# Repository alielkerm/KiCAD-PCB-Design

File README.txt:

# Project Name

KiCAD PCB Designs

## Overview
This directory shows some personal as well as professional projects in PCB design using KiCAD open source tool.

## Context
Academic / personal project related to space electronics, payload design, amateur boards for learning and teaching to bachelor and master students.

## Technologies
- KiCAD

## Results
Boards are ready to be sent to the manufacturing house, once the PCB boards are fabricated, I will share the physical boards, the tests and the results of the tests.

## Author
Ali Elkerm

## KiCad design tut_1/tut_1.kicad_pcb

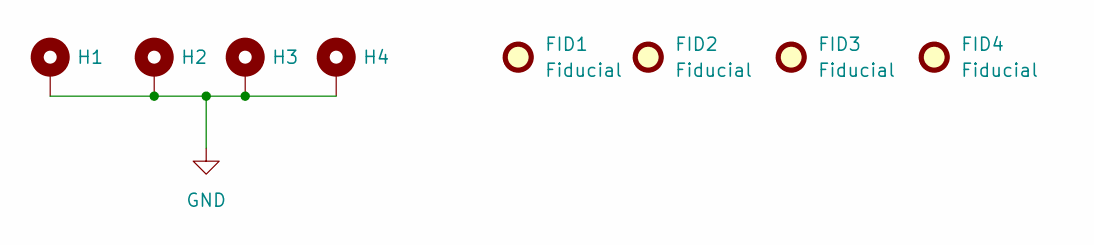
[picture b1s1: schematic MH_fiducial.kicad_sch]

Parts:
FID1, FID2, FID3, FID4: Fiducial; Fiducial_1.5mm_Mask3mm
H1, H2, H3, H4: MountingHole_Pad; MountingHole_2.5mm_Pad

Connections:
GND: H1.1, H2.1, H3.1, H4.1; also elsewhere on the board

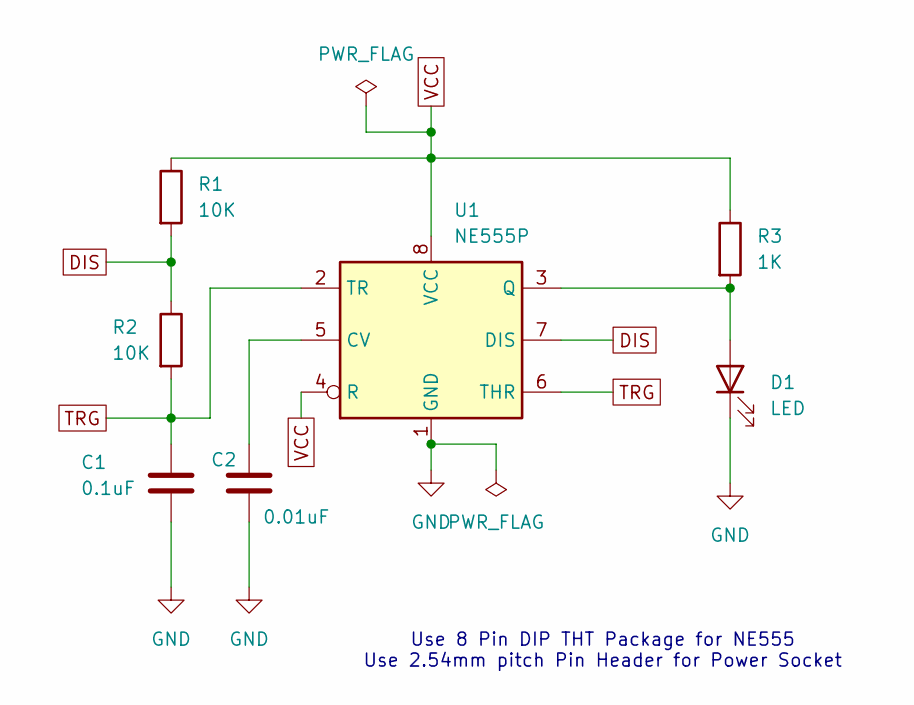
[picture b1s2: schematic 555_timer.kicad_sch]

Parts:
C1: 0.1uF; C_0603_1608Metric
C2: 0.01uF; C_0603_1608Metric
D1: LED; LED_0603_1608Metric
R1, R2: 10K; R_0603_1608Metric
R3: 1K; R_0603_1608Metric
U1: NE555P; SOP-8_3.76x4.96mm_P1.27mm

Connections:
DIS: R1.2, R2.1, U1.7 (DIS)
GND: C1.2, C2.2, D1.1 (K), U1.1 (GND); also elsewhere on the board
unnamed: D1.2 (A), R3.2, U1.3 (Q)
unnamed: C2.1, U1.5 (CV)
TRG: C1.1, R2.2, U1.2 (TR), U1.6 (THR)
VCC: R1.1, R3.1, U1.4 (R), U1.8 (VCC); also elsewhere on the board

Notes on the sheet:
Use 8 Pin DIP THT Package for NE555 Use 2.54mm pitch Pin Header for Power Socket

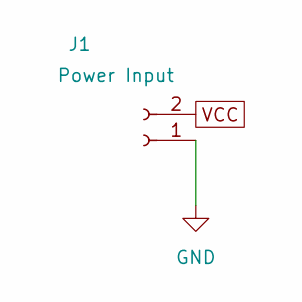
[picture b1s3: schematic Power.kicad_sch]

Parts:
J1: Power Input; PinHeader_1x02_P2.54mm_Vertical

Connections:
GND: J1.1; also elsewhere on the board
VCC: J1.2; also elsewhere on the board

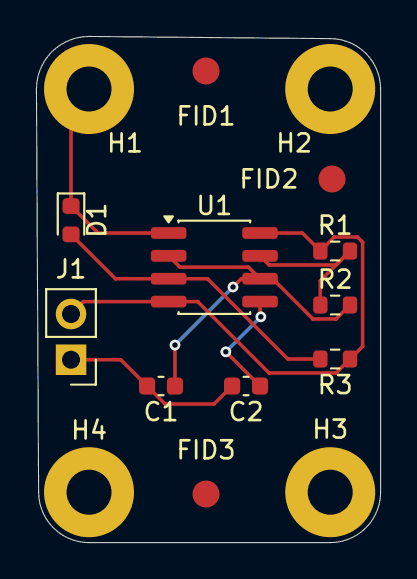
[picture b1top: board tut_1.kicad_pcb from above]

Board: 2 copper layers, 19.1 x 28.1 mm, 15 parts (0 on the bottom side), 6 nets.

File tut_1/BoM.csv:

"Reference","Qty","Value","DNP","Exclude from BOM","Exclude from Board","Footprint","Datasheet"
"C1","1","0.1uF","","","","Capacitor_SMD:C_0603_1608Metric","~"
"C2","1","0.01uF","","","","Capacitor_SMD:C_0603_1608Metric","~"
"D1","1","LED","","","","LED_SMD:LED_0603_1608Metric","~"
"FID1,FID2,FID3,FID4","4","Fiducial","","Excluded from BOM","","Fiducial:Fiducial_1.5mm_Mask3mm","~"
"H1,H2,H3,H4","4","MountingHole_Pad","","Excluded from BOM","","MountingHole:MountingHole_2.5mm_Pad","~"
"J1","1","Power Input","","","","Connector_PinHeader_2.54mm:PinHeader_1x02_P2.54mm_Vertical","~"
"R1,R2","2","10K","","","","Resistor_SMD:R_0603_1608Metric","~"
"R3","1","1K","","","","Resistor_SMD:R_0603_1608Metric","~"
"U1","1","NE555P","","","","Package_SO:SOP-8_3.76x4.96mm_P1.27mm","http://www.ti.com/lit/ds/symlink/ne555.pdf"

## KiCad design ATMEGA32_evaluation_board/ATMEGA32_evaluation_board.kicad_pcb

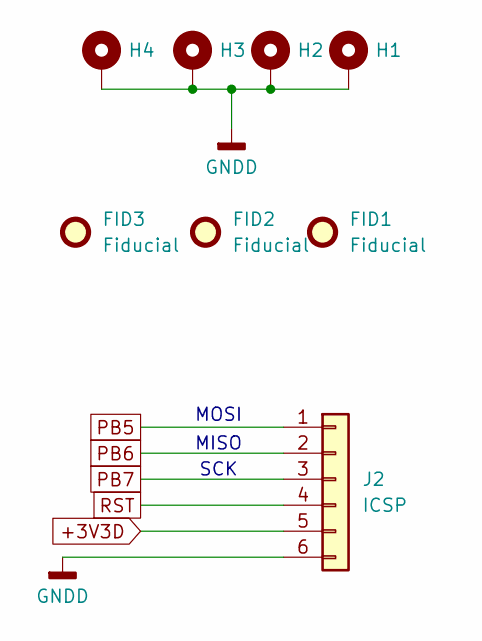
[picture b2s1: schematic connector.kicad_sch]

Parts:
FID1, FID2, FID3: Fiducial; Fiducial_1.5mm_Mask3mm
H1, H2, H3, H4: MountingHole_Pad; MountingHole_2.5mm_Pad
J2: ICSP; PinHeader_1x06_P2.54mm_Vertical

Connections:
+3V3D: J2.5; also elsewhere on the board
GNDD: H1.1, H2.1, H3.1, H4.1, J2.6; also elsewhere on the board
PB5: J2.1; also elsewhere on the board
PB6: J2.2; also elsewhere on the board
PB7: J2.3; also elsewhere on the board
RST: J2.4; also elsewhere on the board

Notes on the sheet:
MISO
MOSI
SCK

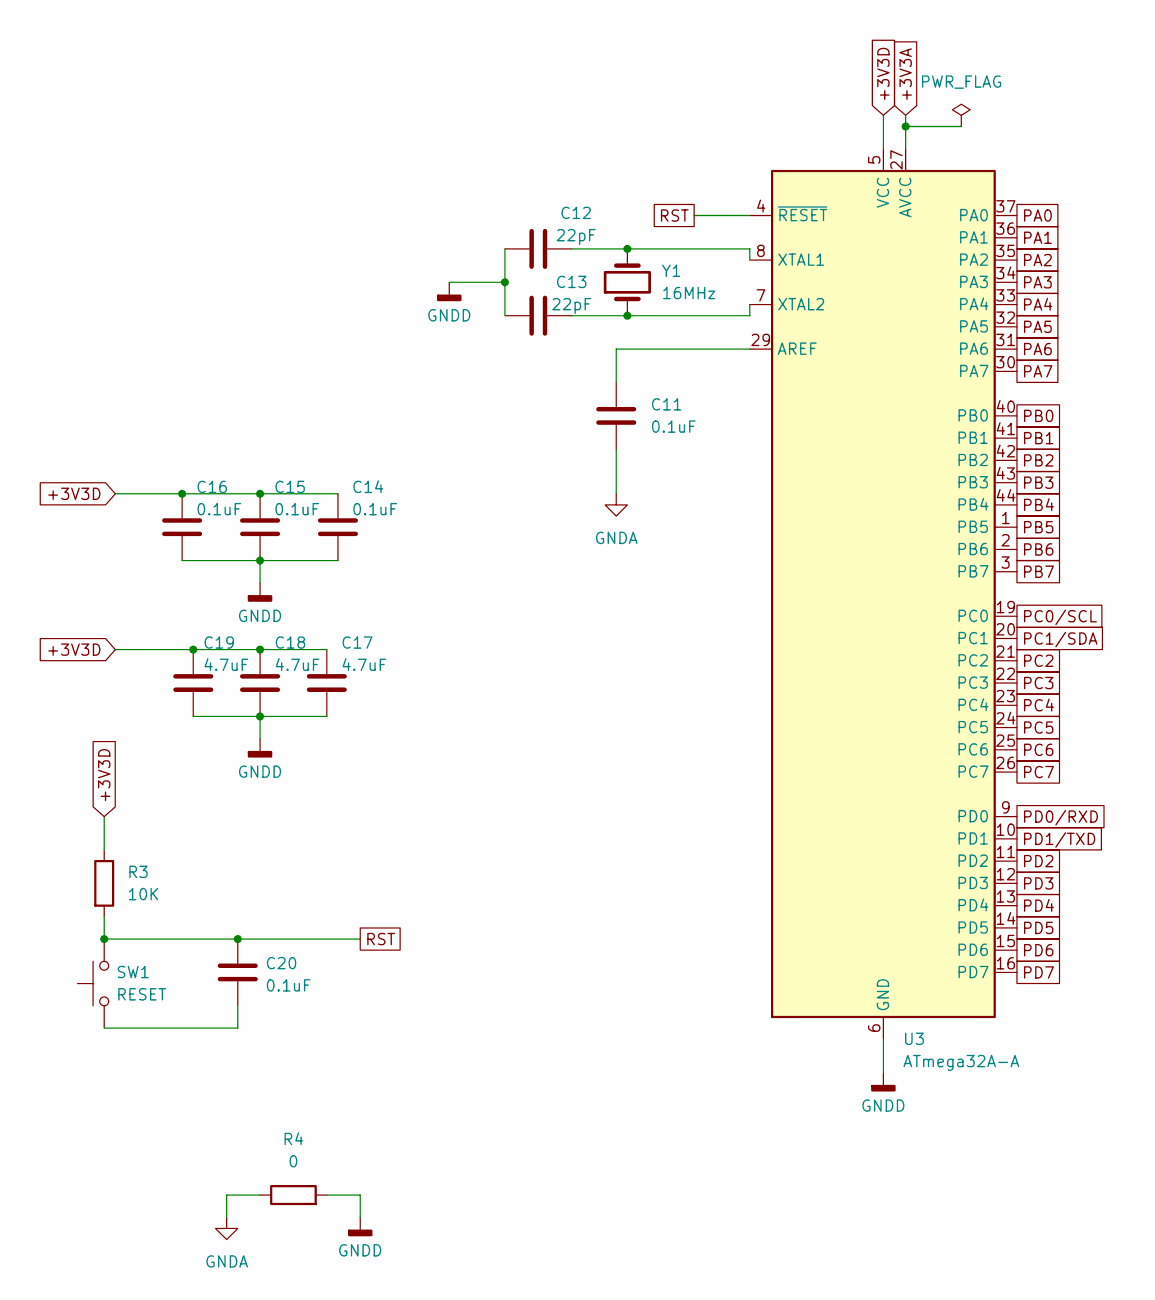
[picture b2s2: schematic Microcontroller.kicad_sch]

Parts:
C11, C14, C15, C16, C20: 0.1uF; C_0603_1608Metric
C12, C13: 22pF; C_0603_1608Metric
C17, C18, C19: 4.7uF; C_0603_1608Metric
R3: 10K; R_0603_1608Metric
R4: 0; R_0603_1608Metric
SW1: RESET; SW_PUSH_6mm
U3: ATmega32A-A; TQFP-44_10x10mm_P0.8mm
Y1: 16MHz; Crystal_SMD_0603-2Pin_6.0x3.5mm

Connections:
+3V3A: U3.27 (AVCC); also elsewhere on the board
+3V3D: C14.1, C15.1, C16.1, C17.1, C18.1, C19.1, R3.1, U3.5 (VCC), U3.17 (VCC), U3.38 (VCC); also elsewhere on the board
GNDA: C11.2, R4.1; also elsewhere on the board
GNDD: C12.1, C13.2, C14.2, C15.2, C16.2, C17.2, C18.2, C19.2, R4.2, U3.6 (GND), U3.18 (GND), U3.28 (GND), U3.39 (GND); also elsewhere on the board
unnamed: C20.2, SW1.1
unnamed: C11.1, U3.29 (AREF)
unnamed: C12.2, U3.8 (XTAL1), Y1.2
unnamed: C13.1, U3.7 (XTAL2), Y1.1
PA0: U3.37 (PA0)
PA1: U3.36 (PA1)
PA2: U3.35 (PA2)
PA3: U3.34 (PA3)
PA4: U3.33 (PA4)
PA5: U3.32 (PA5)
PA6: U3.31 (PA6)
PA7: U3.30 (PA7)
PB0: U3.40 (PB0)
PB1: U3.41 (PB1)
PB2: U3.42 (PB2)
PB3: U3.43 (PB3)
PB4: U3.44 (PB4)
PB5: U3.1 (PB5); also elsewhere on the board
PB6: U3.2 (PB6); also elsewhere on the board
PB7: U3.3 (PB7); also elsewhere on the board
PC0/SCL: U3.19 (PC0)
PC1/SDA: U3.20 (PC1)
PC2: U3.21 (PC2)
PC3: U3.22 (PC3)
PC4: U3.23 (PC4)
PC5: U3.24 (PC5)
PC6: U3.25 (PC6)
PC7: U3.26 (PC7)
PD0/RXD: U3.9 (PD0)
PD1/TXD: U3.10 (PD1)
PD2: U3.11 (PD2)
PD3: U3.12 (PD3)
PD4: U3.13 (PD4)
PD5: U3.14 (PD5)
PD6: U3.15 (PD6)
PD7: U3.16 (PD7)
RST: C20.1, R3.2, SW1.2, U3.4 (~RESET); also elsewhere on the board

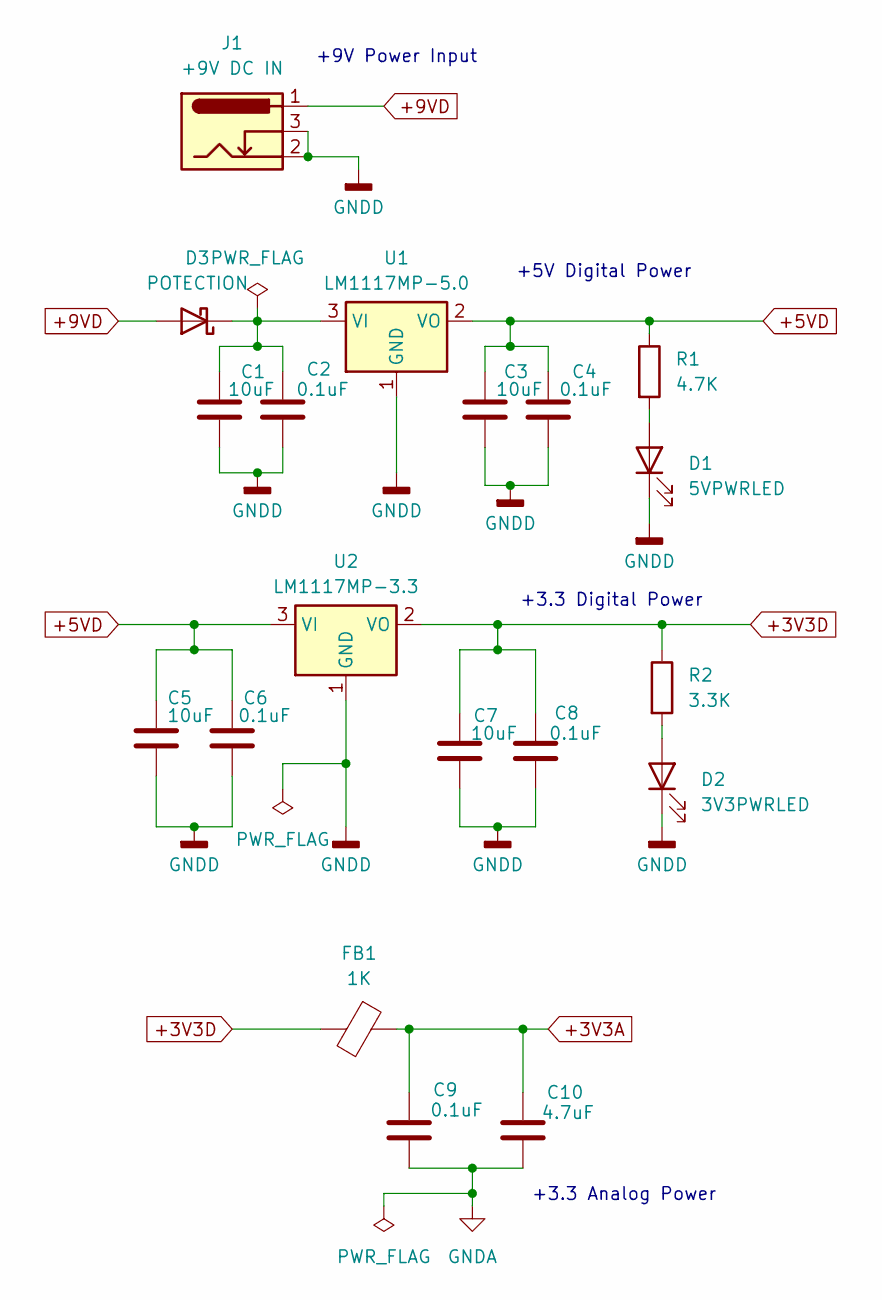
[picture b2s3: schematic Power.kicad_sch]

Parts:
C1, C3, C5, C7: 10uF; C_0603_1608Metric
C2, C4, C6, C8, C9: 0.1uF; C_0603_1608Metric
C10: 4.7uF; C_0603_1608Metric
D1: 5VPWRLED; LED_0603_1608Metric
D2: 3V3PWRLED; LED_0603_1608Metric
D3: POTECTION; D_SMA
FB1: 1K; L_0603_1608Metric
J1: +9V DC IN; PinHeader_1x03_P2.54mm_Vertical
R1: 4.7K; R_0603_1608Metric
R2: 3.3K; R_0603_1608Metric
U1: LM1117MP-5.0; SOT-223-3_TabPin2
U2: LM1117MP-3.3; SOT-223-3_TabPin2

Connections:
+3V3A: C9.1, C10.1, FB1.1; also elsewhere on the board
+3V3D: C7.1, C8.1, FB1.2, R2.1, U2.2 (VO); also elsewhere on the board
+5VD: C3.1, C4.1, C5.1, C6.1, R1.1, U1.2 (VO), U2.3 (VI)
+9VD: D3.2 (A), J1.1
GNDA: C9.2, C10.2; also elsewhere on the board
GNDD: C1.2, C2.2, C3.2, C4.2, C5.2, C6.2, C7.2, C8.2, D1.1 (K), D2.1 (K), J1.2, J1.3, U1.1 (GND), U2.1 (GND); also elsewhere on the board
unnamed: D1.2 (A), R1.2
unnamed: D2.2 (A), R2.2
unnamed: C1.1, C2.1, D3.1 (K), U1.3 (VI)

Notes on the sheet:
+9V Power Input
+5V Digital Power
+3.3 Analog Power
+3.3 Digital Power

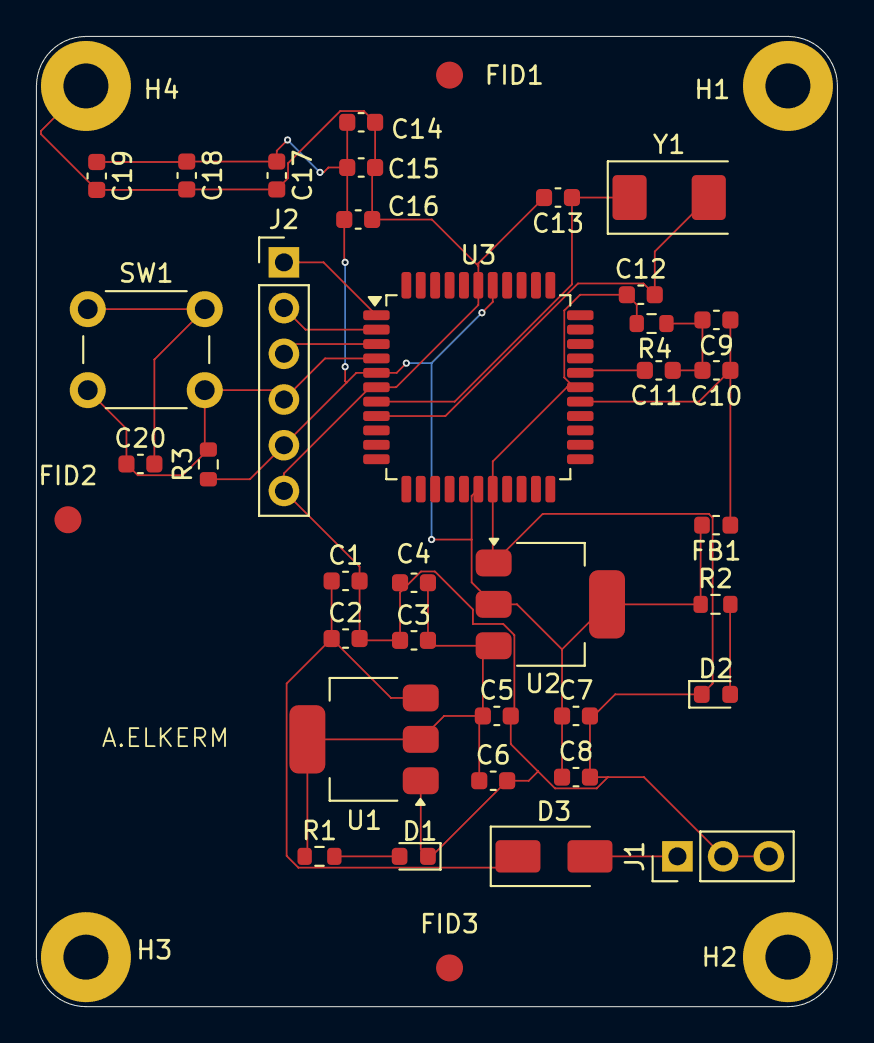
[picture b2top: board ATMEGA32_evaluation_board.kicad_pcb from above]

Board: 4 copper layers, 44.5 x 53.9 mm, 42 parts (0 on the bottom side), 17 nets.

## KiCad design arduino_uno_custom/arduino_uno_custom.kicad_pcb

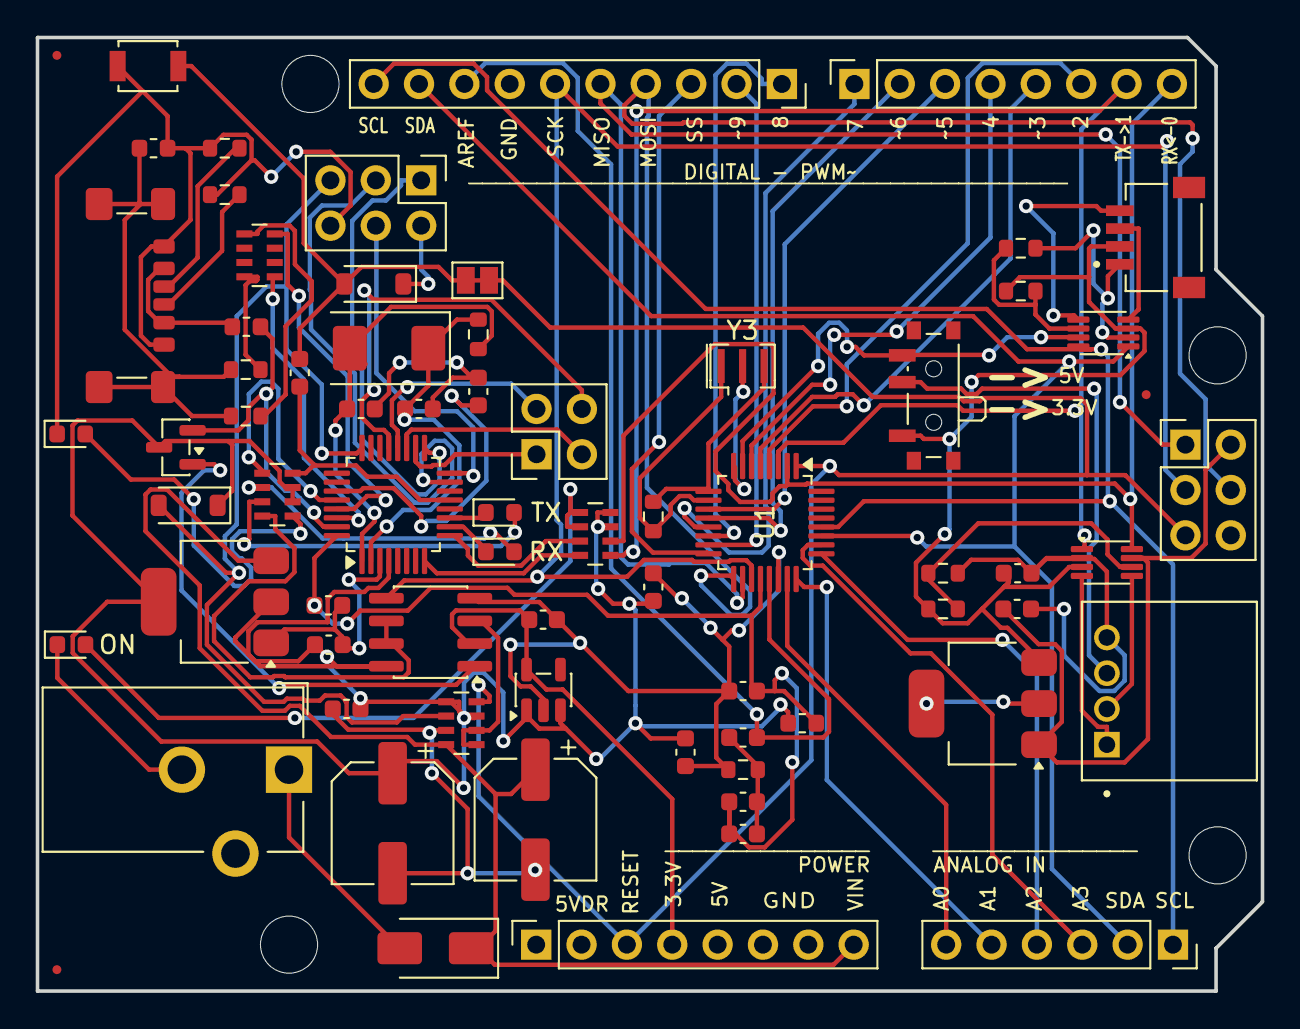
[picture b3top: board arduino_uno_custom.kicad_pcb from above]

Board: 4 copper layers, 68.6 x 53.4 mm, 75 parts (0 on the bottom side), 71 nets.

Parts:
C3, C4, C5, C6, C9, C10, C13, C14, C18, C19: 0.1uF; C_0603_1608Metric
C7, C8: 22pF; C_0603_1608Metric
C11, C12: 1uF; C_0603_1608Metric
C15: 4.7uF; C_0603_1608Metric
C16, C17: 47uF; CP_Elec_6.3x5.4
C21: 2.2uF; C_0603_1608Metric
D1, D2: 1N4148; D_SOD-123
D3: YELLOW; LED_0603_1608Metric
D4: 1N4148; D_SMA
F1: Polyfuse; Fuse_0603_1608Metric
FB1: FerriteBead; L_0603_1608Metric
FB2: 1K; L_0603_1608Metric
FID1, FID2, FID3: Fiducial; Fiducial_0.5mm_Mask1.5mm
H1, H2, H3, H4: MountingHole_Pad; MountingHole_3.2mm_M3
ICSP1: 3x2M; PinHeader_2x03_P2.54mm_Vertical
J1: 3x2M; PinHeader_2x03_P2.54mm_Vertical
J2: 2x2M; PinHeader_2x02_P2.54mm_Vertical
J3: PRT-14417; QWIIC_SPARKFUN_14417
J4: Conn_01x10_Socket; PinSocket_1x10_P2.54mm_Vertical
J5: POWER; PinSocket_1x06_P2.54mm_Vertical
J6, J7: Conn_01x08_Socket; PinSocket_1x08_P2.54mm_Vertical
J8: USB_C_Receptacle_USB2.0_16P; USB_C_Receptacle_GCT_USB4135-GF-A_6P_TopMnt_Horizontal
J9: 110990037; Grove_Seeed_90d_110990037
ON: GREEN; LED_0603_1608Metric
Q1: FDN340P; SOT-23
R1, R3: 1M; R_0603_1608Metric
R2: 0; R_0603_1608Metric
R4, R5, R9, R11: 10K; R_0603_1608Metric
R6, R7: 5.1K; R_0603_1608Metric
R8, R10: 100K; R_0603_1608Metric
RESET-EN1: SolderJumper_2_Open; SolderJumper-2_P1.3mm_Open_Pad1.0x1.5mm
RN1: 10K; R_Array_Concave_4x0603
RN2, RN4: 1K; R_Array_Concave_4x0603
RN3: 22R; R_Array_Concave_4x0603
RX: YELLOW; LED_0603_1608Metric
SW1: RESET; SW_SPST_B3U-1000P
SW2: SW_SPDT; SW_SPDT_PCM12
TX: YELLOW; LED_0603_1608Metric
U1: ATmega328P-P; TQFP-32_5x5mm_P0.5mm
U2: ATmega16U2-M; TQFP-32_5x5mm_P0.5mm
U3: LP2985-3.3; SOT-23-5
U4: LMV358; SOIC-8_3.9x4.9mm_P1.27mm
U5: NCP1117-5.0_SOT223; SOT-223-3_TabPin2
U6: SPX2920M3-3.3_SOT223; SOT-223-3_TabPin2
U7, U8: TXS0102DCU; VSSOP-8_2.3x2mm_P0.5mm
X1: POWERSUPPLY; BarrelJack_CUI_PJ-102AH_Horizontal
Y2: 16MHz; Crystal_SMD_0603-2Pin_6.0x3.5mm
Y3: Resonator; Resonator_SMD_Murata_CSTxExxV-3Pin_3.0x1.1mm

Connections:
+3V3D: C12.1, J7.4, U3.5 (VOUT), U4.2 (-)
+3V3Dbig: C21.2, J3.2, R9.1, R11.1, SW2.1 (A), U6.3 (VO), U7.3 (VCCA), U8.3 (VCCA)
+5VA: C5.2, C10.2, C14.1, C15.1, FB2.1, U1.20 (AVCC), U2.32 (AVCC)
+5VD: C4.2, C9.2, C13.1, C17.1, C18.2, C19.2, D1.1 (K), D2.1 (K), FB2.2, ICSP1.2, J1.2, J7.2, J7.5, Q1.3 (D), RN1.3 (R3.1), RN1.5 (R4.2), RN2.2 (R2.1), RN2.3 (R3.1), RN4.3 (R3.1), RN4.4 (R4.1), SW2.3 (C), U1.7 (VCC), U2.4 (VCC), U3.1 (VIN), U3.3 (ON/~OFF), U4.8 (V+), U5.2 (VO), U6.1 (VI), U7.7 (VCCB), U8.7 (VCCB)
/ATmega16U2/DTR: C6.1, RN2.4 (R4.1), U2.13 (~HWB/PD7)
/ATmega16U2/PB4: J2.1, U2.18 (PB4)
/ATmega16U2/PB5: J2.3, U2.19 (PB5)
/ATmega16U2/PB6: J2.2, U2.20 (PB6)
/ATmega16U2/PB7: J2.4, U2.21 (PB7)
/ATmega16U2/RXD: J6.8, RN4.2 (R2.1), U1.2 (PD0), U7.8 (B1)
/ATmega16U2/TXD: J6.7, RN4.1 (R1.1), U1.3 (PD1), U7.1 (B2)
/ATmega16U2/USBVCC: F1.2, Q1.2 (S), U2.31 (UVCC)
/ATmega328p/AD0: J5.6, U1.23 (PC0)
/ATmega328p/AD1: J5.5, U1.24 (PC1)
/ATmega328p/AD2: J5.4, U1.25 (PC2)
/ATmega328p/AD3: J5.3, U1.26 (PC3)
/ATmega328p/AREF: C3.2, J4.8, U1.21 (AREF)
/ATmega328p/MISO: ICSP1.1, J4.5, U1.18 (PB4)
/ATmega328p/MOSI: ICSP1.4, J4.4, U1.17 (PB3)
/ATmega328p/PB0/ICP: J4.1, U1.14 (PB0)
/ATmega328p/PB1/OC1: J4.2, U1.15 (PB1)
/ATmega328p/PD2: J6.6, U1.4 (PD2)
/ATmega328p/PD3: J6.5, U1.5 (PD3)
/ATmega328p/PD4: J6.4, U1.6 (PD4)
/ATmega328p/PD5: J6.3, U1.11 (PD5)
/ATmega328p/PD6: J6.2, U1.12 (PD6)
/ATmega328p/PD7: J6.1, U1.13 (PD7)
/ATmega328p/SCK: ICSP1.3, J4.6, U1.19 (PB5), U4.5 (+)
/ATmega328p/SCL: J4.10, J5.1, U1.28 (PC5), U8.8 (B1)
/ATmega328p/SDA: J4.9, J5.2, U1.27 (PC4), U8.1 (B2)
/ATmega328p/SS: J4.3, U1.16 (PB2)
/ATmega328p/~RESET/PC6: C6.2, D1.2 (A), ICSP1.5, J7.3, RESET-EN1.1 (A), RESET-EN1.2 (B), RN1.4 (R4.1), SW1.1, U1.1 (~RESET/PC6)
/connector/VIN: C16.1, D4.1 (K), J7.8, RN1.8 (R1.2), U5.3 (VI)
D+: RN3.4 (R4.1), U2.29 (D+)
D-: RN3.1 (R1.1), U2.30 (D-)
GNDA: C3.1, C14.2, C15.2, R2.1
GNDD: C4.1, C5.1, C7.1, C8.1, C9.1, C10.1, C11.2, C12.2, C13.2, C16.2, C17.2, C18.1, C19.1, C21.1, D3.1 (K), FB1.2, ICSP1.6, J1.6, J3.1, J4.7, J7.6, J7.7, J8.A12 (GND), J8.B12 (GND), J9.4, ON.1 (K), R2.2, R6.2, R7.2, R8.1, R10.1, RN1.7 (R2.2), RN2.5 (R4.2), SW1.2, U1.8 (GND), U1.22 (GND), U2.3 (GND), U2.28 (UGND), U3.2 (GND), U4.4 (V-), U5.1 (GND), U6.2 (GND), U7.2 (GND), U8.2 (GND), X1.2, X1.3, Y3.2
MISO2: J1.1, U2.17 (PB3)
MOSI2: J1.4, U2.16 (PB2)
unnamed: D3.2 (A), RN2.1 (R1.1)
unnamed: D4.2 (A), X1.1
unnamed: F1.1, J8.A9 (VBUS), J8.B9 (VBUS)
unnamed: J8.A5 (CC1), R6.1
unnamed: J8.B5 (CC2), R7.1
unnamed: ON.2 (A), RN4.5 (R4.2), RN4.6 (R3.2)
unnamed: Q1.1 (G), U4.1
unnamed: RN1.1 (R1.1), RN1.2 (R2.1), U4.3 (+)
unnamed: RN2.8 (R1.2), U4.6 (-), U4.7
unnamed: RN2.7 (R2.2), TX.2 (A)
unnamed: RN2.6 (R3.2), RX.2 (A)
unnamed: R4.1, RN3.8 (R1.2)
unnamed: R5.1, RN3.5 (R4.2)
unnamed: RN4.8 (R1.2), U2.8 (PD2)
unnamed: RN4.7 (R2.2), U2.9 (PD3)
unnamed: RX.1 (K), U2.10 (PD4)
unnamed: J9.3, SW2.2 (B)
unnamed: TX.1 (K), U2.11 (PD5)
unnamed: R1.1, U1.9 (XTAL1/PB6), Y3.3
unnamed: R1.2, U1.10 (XTAL2/PB7), Y3.1
unnamed: C8.2, R3.2, U2.2 (PC0/XTAL2), Y2.1
unnamed: C11.1, U2.27 (UCAP)
unnamed: C7.2, R3.1, U2.1 (XTAL1), Y2.2
unnamed: J9.2, U7.5 (A1)
unnamed: J9.1, U7.4 (A2)
unnamed: R8.2, R9.2, U7.6 (OE)
unnamed: J3.4, U8.5 (A1)
unnamed: J3.3, U8.4 (A2)
unnamed: R10.2, R11.2, U8.6 (OE)
RST: D2.2 (A), J1.5, RN1.6 (R3.2), U2.24 (PC1/~RESET)
SCK2: J1.3, U2.15 (PB1)
USHD: FB1.1, J8.S1 (SHIELD), R4.2, R5.2

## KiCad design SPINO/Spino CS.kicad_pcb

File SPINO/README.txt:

SPINO is a versatile telecommunication solution suitable for nanosatellites and Cubesats.
Operating in UHF and VHF bands, it features tight integration with amateur radio service and the worldwide amateur radio community.
The development of the SPINO SC board was initiated by enthusiats involved in non-profit / educational space projects. Since 2019, 
the project is supported by the joint efforts of two non-profit organizations: AMSAT-Francophone (site.amsat-f.org) and the hackerspace Electrolab (electrolab.fr).

For the context of my projects, I imported SPINO files from the public GitHub (https://code.electrolab.fr/spino/cubesat_cs) for the purpose of having hands on experience in 
generating production files, placing an order from a PCB manufacturing house (JLCPCB), choosing components suitable for the design while soldering some of them 
after the design board is fabricated and delivered and fiinally testing the board in our research lab

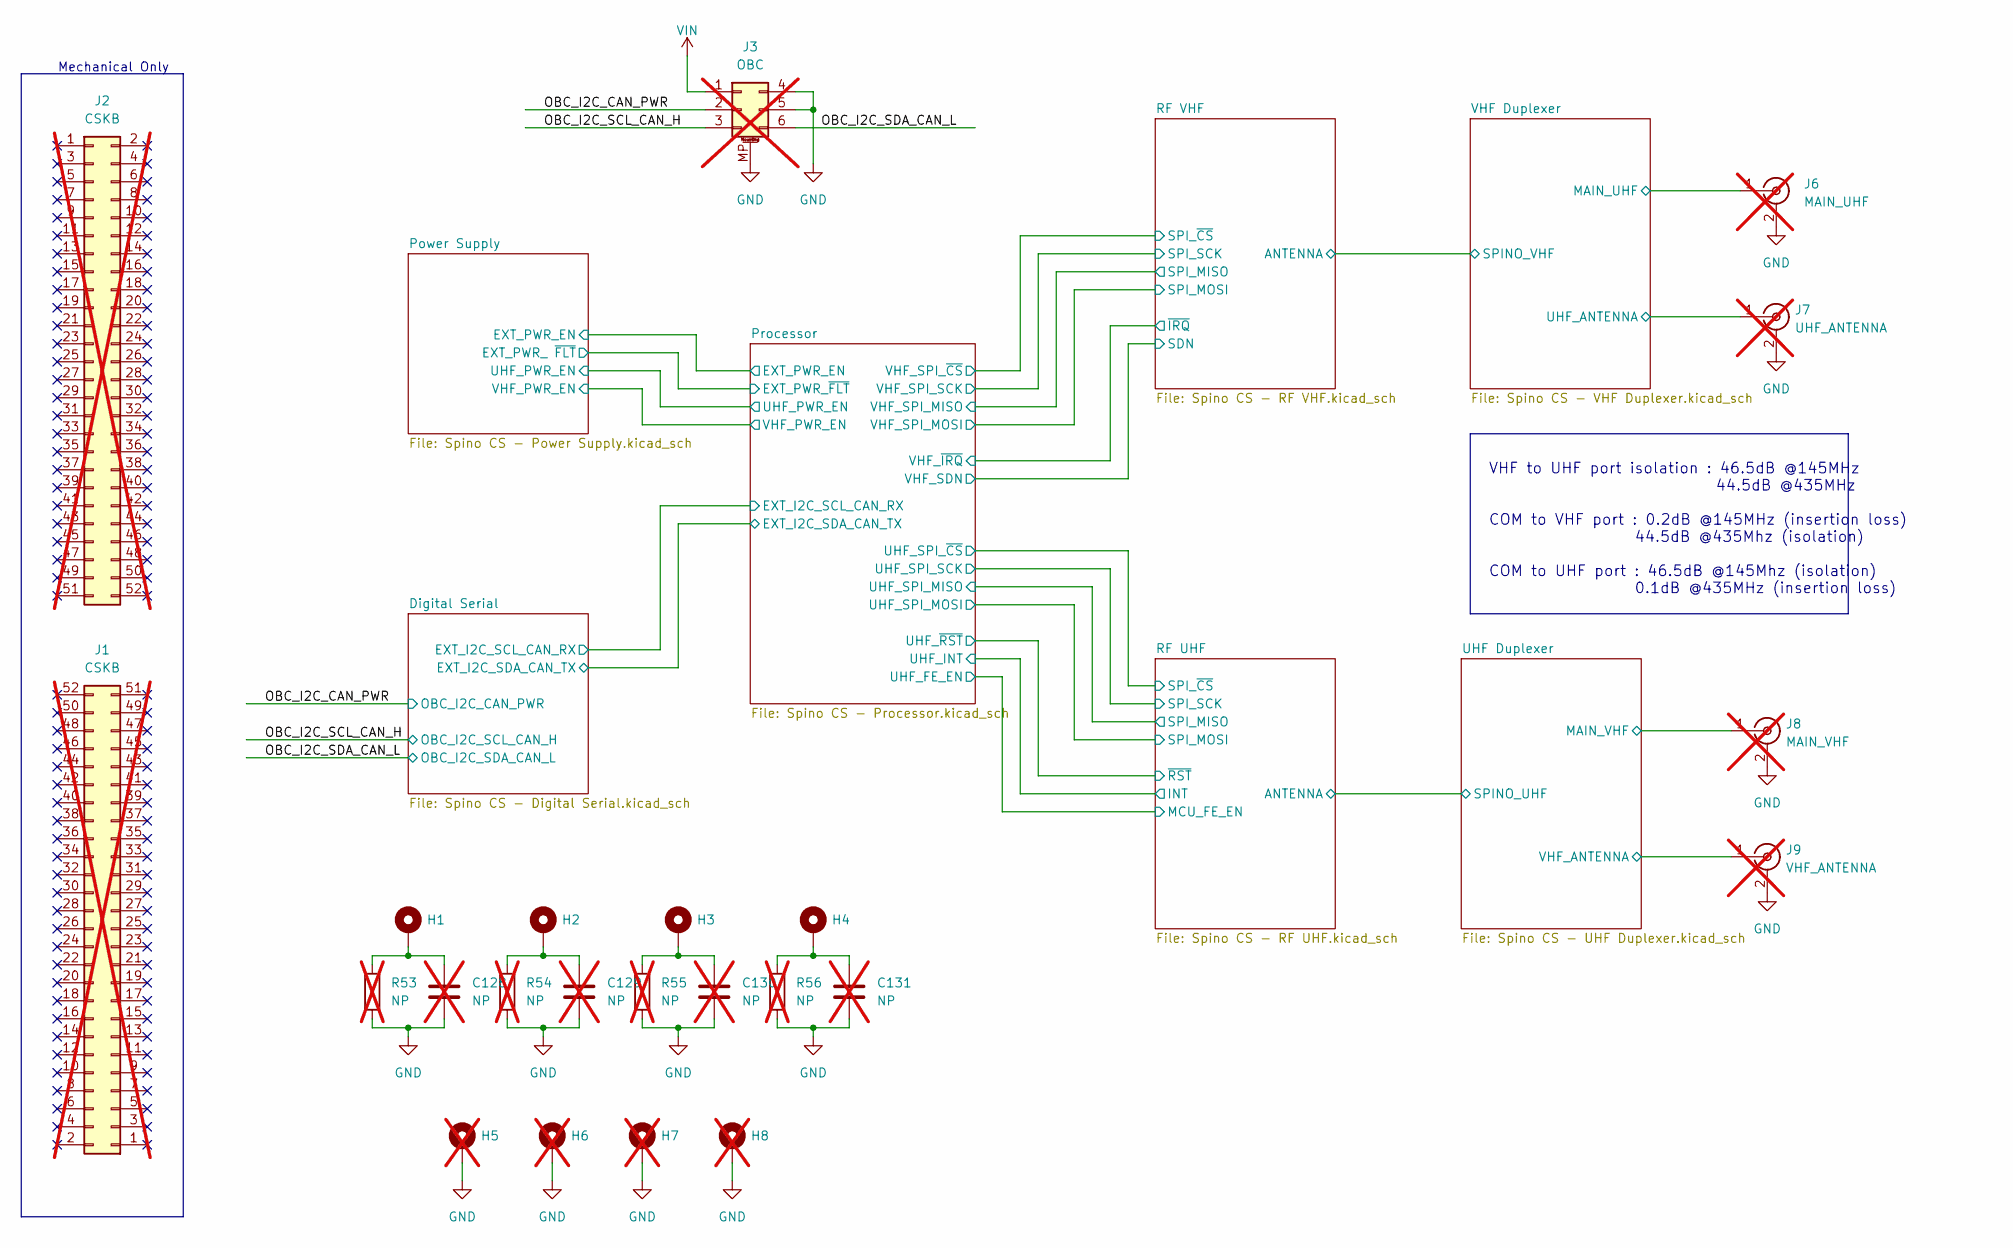
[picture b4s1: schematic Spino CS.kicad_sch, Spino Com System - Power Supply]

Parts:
C128, C129, C130, C131: NP; C_0603_1608Metric; not fitted
H1, H2, H3, H4: MountingHole; MountingHole_3.2mm_M3_Pad
H5, H6, H7, H8: 9774060360; Mounting_Wuerth_WA-SMSI-M3_H6mm_9774060360; not fitted
J1, J2: CSKB; PinHeader_2x26_P2.54mm_Vertical; not fitted
J3: OBC; Harwin_LTek-Male_2x03_P2.00mm_Horizontal_StrainRelief; not fitted
J6: MAIN_UHF; MMCX_Molex_73415-1001_Horizontal; not fitted
J7: UHF_ANTENNA; MMCX_Molex_73415-1001_Horizontal; not fitted
J8: MAIN_VHF; MMCX_Molex_73415-1001_Horizontal; not fitted
J9: VHF_ANTENNA; MMCX_Molex_73415-1001_Horizontal; not fitted
R53, R54, R55, R56: NP; R_0805_2012Metric; not fitted

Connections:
/OBC_I2C_CAN_PWR: J3.2; also elsewhere on the board
/OBC_I2C_SCL_CAN_H: J3.3; also elsewhere on the board
/OBC_I2C_SDA_CAN_L: J3.6; also elsewhere on the board
/UHF Duplexer/MAIN_VHF: J8.1 (In); also elsewhere on the board
/UHF Duplexer/VHF_ANTENNA: J9.1 (In); also elsewhere on the board
/VHF Duplexer/MAIN_UHF: J6.1 (In); also elsewhere on the board
/VHF Duplexer/UHF_ANTENNA: J7.1 (In); also elsewhere on the board
GND: C128.2, C129.2, C130.2, C131.2, H5.1, H6.1, H7.1, H8.1, J3.4, J3.5, J3.MP (MountPin), J6.2 (Ext), J7.2 (Ext), J8.2 (Ext), J9.2 (Ext), R53.2, R54.2, R55.2, R56.2; also elsewhere on the board
unnamed: C128.1, H1.1, R53.1
unnamed: C129.1, H2.1, R54.1
unnamed: C130.1, H3.1, R55.1
unnamed: C131.1, H4.1, R56.1
VIN: J3.1; also elsewhere on the board

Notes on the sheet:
VHF to UHF port isolation : 46.5dB @145MHz 44.5dB @435MHz COM to VHF port : 0.2dB @145MHz (insertion loss) 44.5dB @435Mhz (isolation) COM to UHF port : 46.5dB @145Mhz (isolation) 0.1dB @435MHz (insertion loss)
Mechanical Only

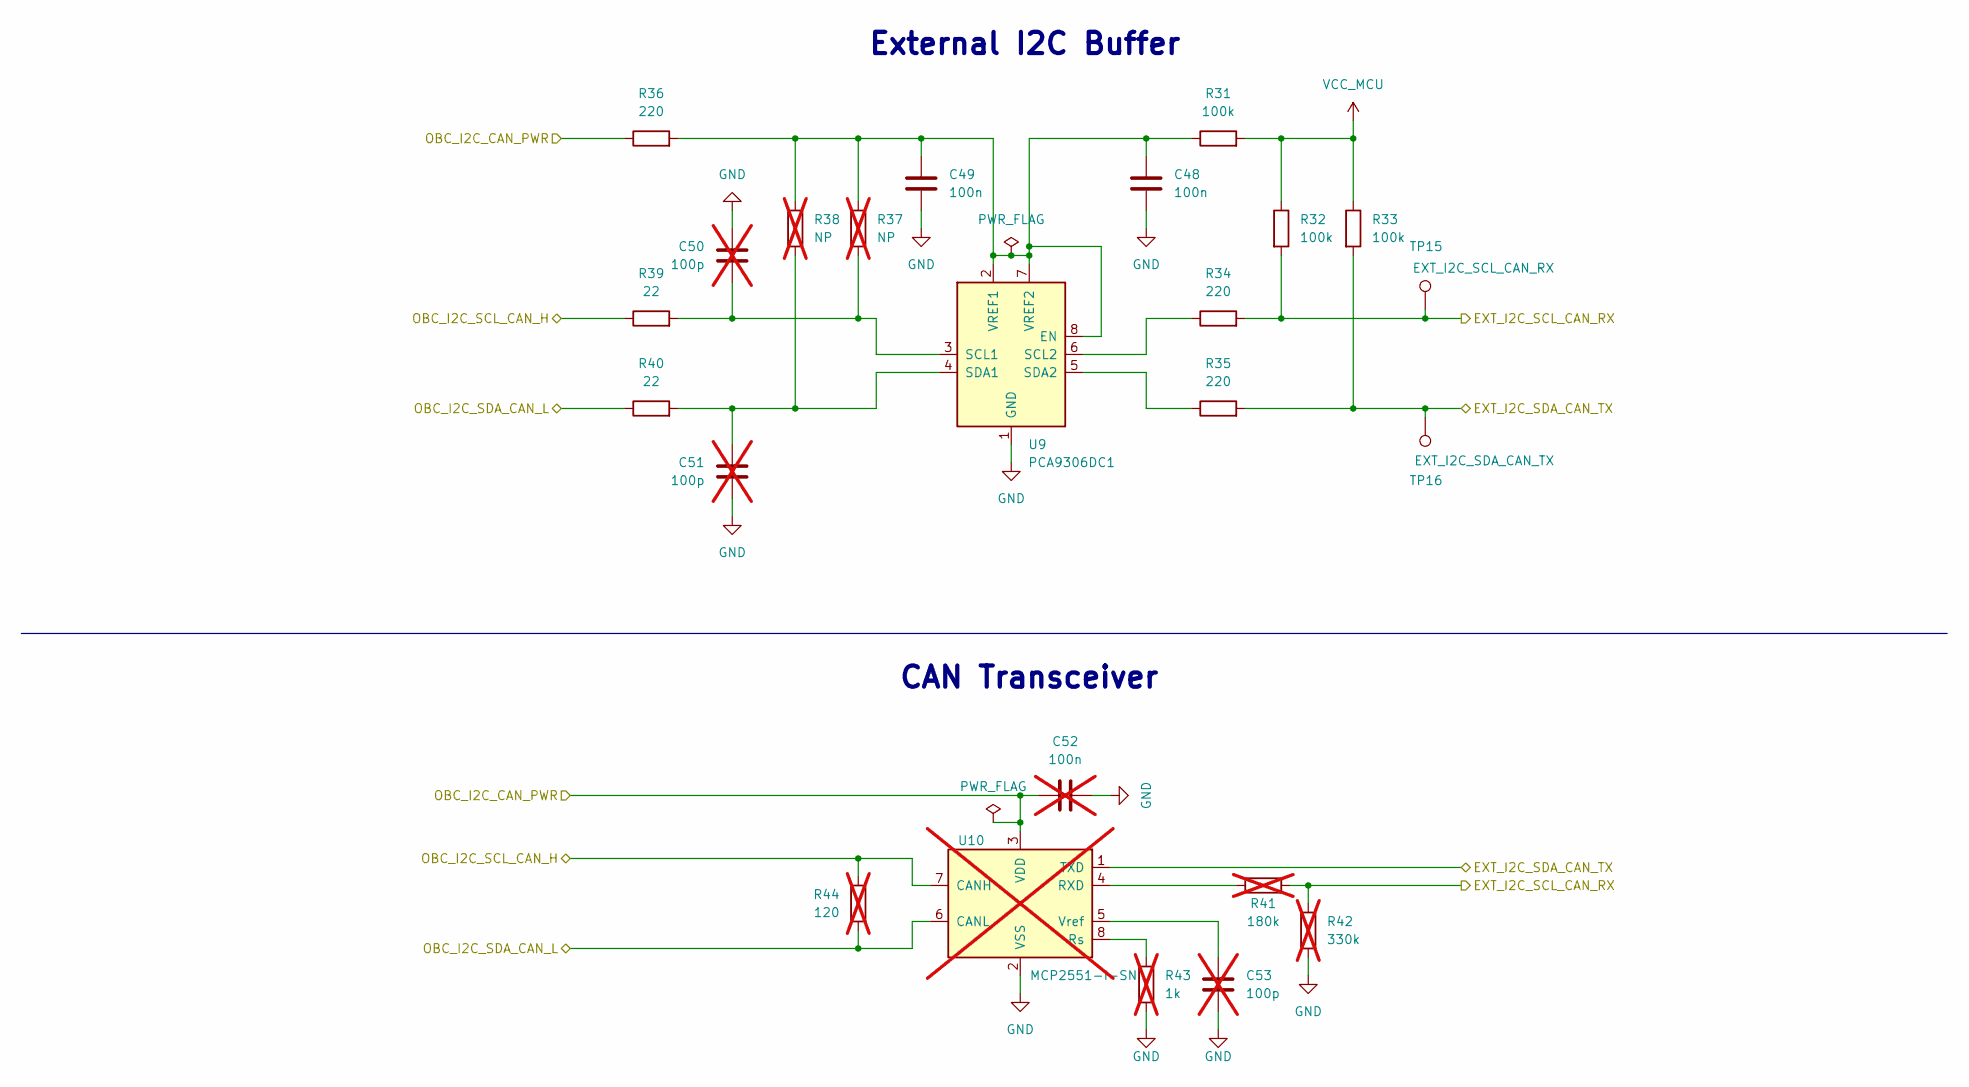
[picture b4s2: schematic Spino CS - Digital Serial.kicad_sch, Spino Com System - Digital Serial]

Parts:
C48, C49: 100n; C_0402_1005Metric
C50, C51, C53: 100p; C_0402_1005Metric; Tolerance 1%; not fitted
C52: 100n; C_0402_1005Metric; not fitted
R31, R32, R33: 100k; R_0402_1005Metric; Tolerance 1%
R34, R35, R36: 220; R_0402_1005Metric; Tolerance 1%
R37, R38: NP; R_0402_1005Metric; not fitted
R39, R40: 22; R_0402_1005Metric; Tolerance 1%
R41: 180k; R_0402_1005Metric; not fitted
R42: 330k; R_0402_1005Metric; not fitted
R43: 1k; R_0402_1005Metric; not fitted
R44: 120; R_0402_1005Metric; not fitted
TP15: EXT_I2C_SCL_CAN_RX; TestPoint_Pad_D1.0mm
TP16: EXT_I2C_SDA_CAN_TX; TestPoint_Pad_D1.0mm
U9: PCA9306DC1; VSSOP-8_2.3x2mm_P0.5mm
U10: MCP2551-I-SN; SOIC-8_3.9x4.9mm_P1.27mm; not fitted

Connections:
/Digital Serial/EXT_I2C_SCL_CAN_RX: R32.2, R34.2, R41.1, R42.1, TP15.1; also elsewhere on the board
/Digital Serial/EXT_I2C_SDA_CAN_TX: R33.2, R35.2, TP16.1, U10.1 (TXD); also elsewhere on the board
/OBC_I2C_CAN_PWR: C52.2, R36.1, U10.3 (VDD); also elsewhere on the board
/OBC_I2C_SCL_CAN_H: R39.1, R44.1, U10.7 (CANH); also elsewhere on the board
/OBC_I2C_SDA_CAN_L: R40.1, R44.2, U10.6 (CANL); also elsewhere on the board
GND: C48.2, C49.2, C50.2, C51.2, C52.1, C53.2, R42.2, R43.2, U9.1 (GND), U10.2 (VSS); also elsewhere on the board
unnamed: C50.1, R37.2, R39.2, U9.3 (SCL1)
unnamed: R34.1, U9.6 (SCL2)
unnamed: C51.1, R38.2, R40.2, U9.4 (SDA1)
unnamed: R35.1, U9.5 (SDA2)
unnamed: R41.2, U10.4 (RXD)
unnamed: R43.1, U10.8 (Rs)
unnamed: C53.1, U10.5 (Vref)
VCC_MCU: R31.2, R32.1, R33.1; also elsewhere on the board

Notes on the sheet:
External I2C Buffer
CAN Transceiver
